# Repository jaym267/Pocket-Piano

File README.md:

Designed a Pocket-Piano, which is an 8-key mini synthesizer. Each key plays one note of a C major scale, from C4 to C5, and a knob shifts every key down or up an octave. It's built around a C XIAO RP2040 microcontroller and plays sound through a small buzzer.
This is a design stage. For the schematic on Kicad, I was able to create it through the project library and wired the 8 push buttons to pins D2 through D9, with each button's other side going to the ground, so no resistors were needed. The knob connects to the 3.3V, ground, and analog pin DO. The buzzer connects to pin D1 through a 100 Ω resistor. I used net labels instead of long wires, added power flags, marked unused pins as no connect, and got the light scroll wheel checked with 0 errors.
For the PCB layout, I made a 100 × 50 mm two-layer board with the 8 keys in a row along the bottom, the XIAO, knob, buzzer, and resistor along the top, and M3 mounting holes in all 4 corners. I routed the trace on the front layer via to send the knob signal under the board and flipped both layers with the ground copper.
Finally, for the case and firmware:
For the case, I imported the board's 3D model and worked on creating the 4 standoff screw holes so that it can be screwed on for the mounting holes, and a notch in the back. Also, a USB-C cable can reset XIAO. I also exported it as a STEP and STL for 3D printing.
For the firmware, I use Arduino, which wrote the code in 3 stages:
1. Compiling each one
2. Setting up the pins
3. Checking which keys are pressed and placing it
It's a note with tone and gives it a cooldown between notes so that no keys sound at the same time, and reads a note to switch between 3 octaves.

# Pocket-Piano
Creating a pocket piano, which is an 8-key mini synthesizer built around XIAO RP2040, with a potentiometer that shifts the octave and a small speaker that plays each note.

## How it works
Each of the 8 keys plays one note of a C major scale (C4 to C5). The knob switches between three octaves: lower, normal, and higher. The XIAO RP2040 reads the buttons and drives a passive buzzer with PWM.

## Schematic

## PCB

## Case
An open-top 3D-printed tray. The board sits on four standoffs and screws in with M3 screws. A notch in the back wall lets a USB-C cable reach the XIAO.

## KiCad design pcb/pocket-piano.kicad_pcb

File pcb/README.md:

KiCad project and gerbers for Pocket Piano.

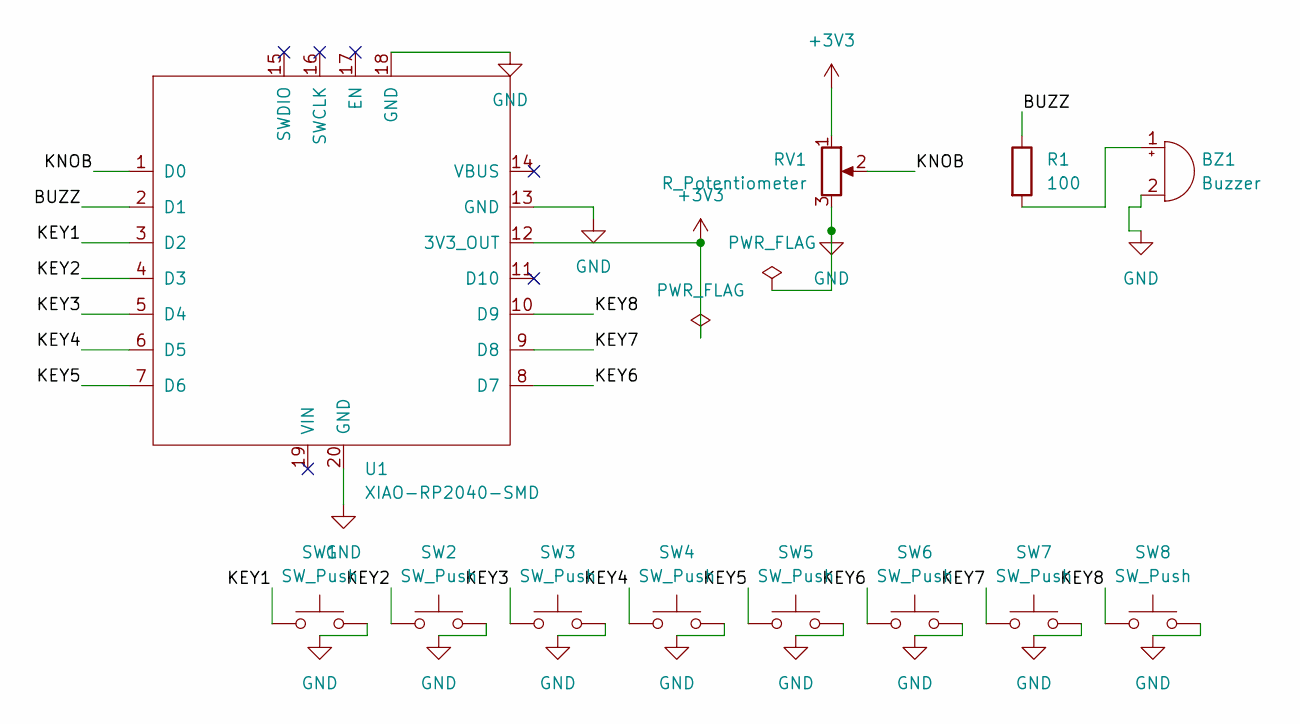
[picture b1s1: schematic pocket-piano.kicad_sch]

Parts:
BZ1: Buzzer; Buzzer_12x9.5RM7.6
R1: 100; R_Axial_DIN0207_L6.3mm_D2.5mm_P7.62mm_Horizontal
RV1: R_Potentiometer; Potentiometer_Alps_RK09K_Single_Vertical
SW1, SW2, SW3, SW4, SW5, SW6, SW7, SW8: SW_Push; SW_PUSH_6mm
U1: XIAO-RP2040-SMD

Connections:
+3V3: RV1.1, U1.12 (3V3_OUT)
/BUZZ: R1.1, U1.2 (D1)
/KEY1: SW1.1, U1.3 (D2)
/KEY2: SW2.1, U1.4 (D3)
/KEY3: SW3.1, U1.5 (D4)
/KEY4: SW4.1, U1.6 (D5)
/KEY5: SW5.1, U1.7 (D6)
/KEY6: SW6.1, U1.8 (D7)
/KEY7: SW7.1, U1.9 (D8)
/KEY8: SW8.1, U1.10 (D9)
/KNOB: RV1.2, U1.1 (D0)
GND: BZ1.2 (-), RV1.3, SW1.2, SW2.2, SW3.2, SW4.2, SW5.2, SW6.2, SW7.2, SW8.2, U1.13 (GND), U1.18 (GND), U1.20 (GND)
unnamed: BZ1.1 (+), R1.2

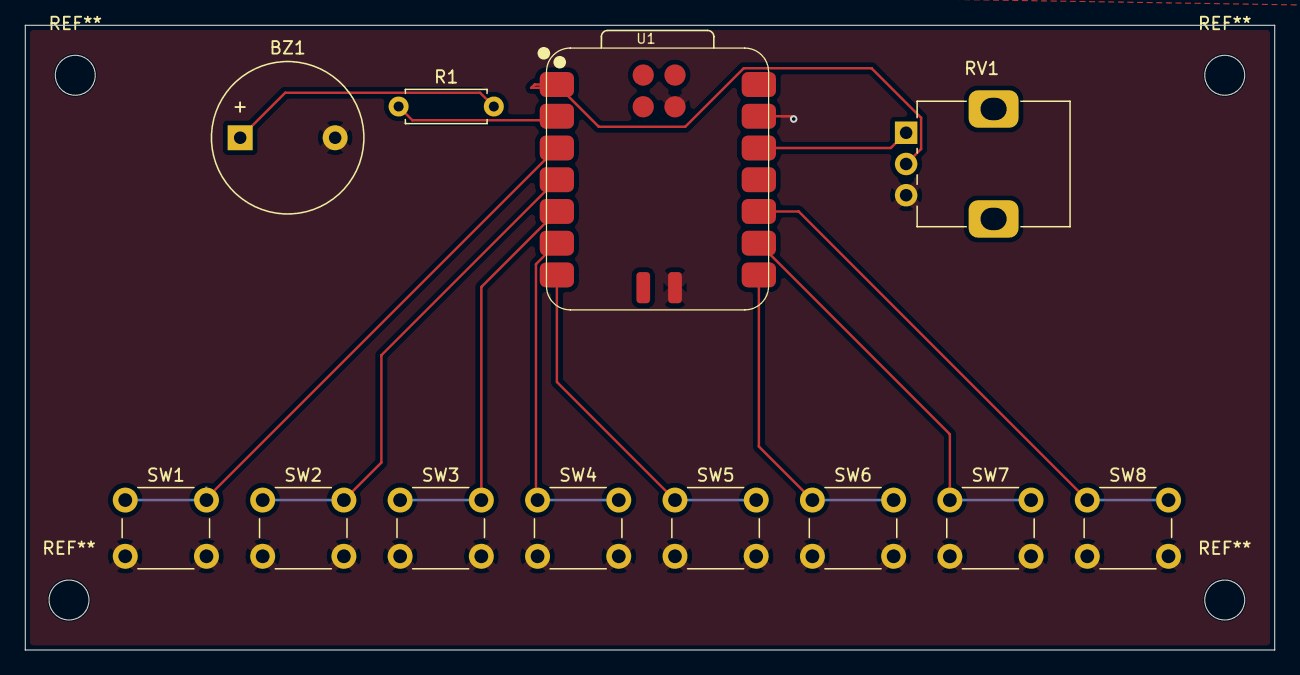
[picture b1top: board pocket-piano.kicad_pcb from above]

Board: 2 copper layers, 100.0 x 50.0 mm, 12 parts (0 on the bottom side), 13 nets.
